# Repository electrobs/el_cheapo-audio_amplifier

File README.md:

# EL CHEAPO AMP

---
    AUTHOR: R.R. Moore (original design), John Convertino(revised)   
    
    DATE: 2020.12.23   
    
    DETAILS: Cheap 2N3055 amplifier using old power supplies for the base. Dual channel opamp version.
---

### DIRECTORY
#### models
3D models
* back_panel.stl  - Back panel for amplifier
* front_panel.stl - Front panel for amplifier
* FOOT.stl        - Foot for amplifier
* pcb.FCStd       - FreeCAD model of circuit board.
* pcb.step        - FreeCAD model of circuit board in STEP format.

#### schematic
KiCad Schematic and PCBS
* el_cheapo.pro - Main KiCAD project file

#### docs
Articles and datasheets used for the project.
* Audio-1964-11.pdf - Original el cheapo Article

### PARTS LIST
* N/A

### BUILD HELP
* This was designed to be built into a Acopian power supply. It depends on your power supply model as to how it will fit together... good luck!

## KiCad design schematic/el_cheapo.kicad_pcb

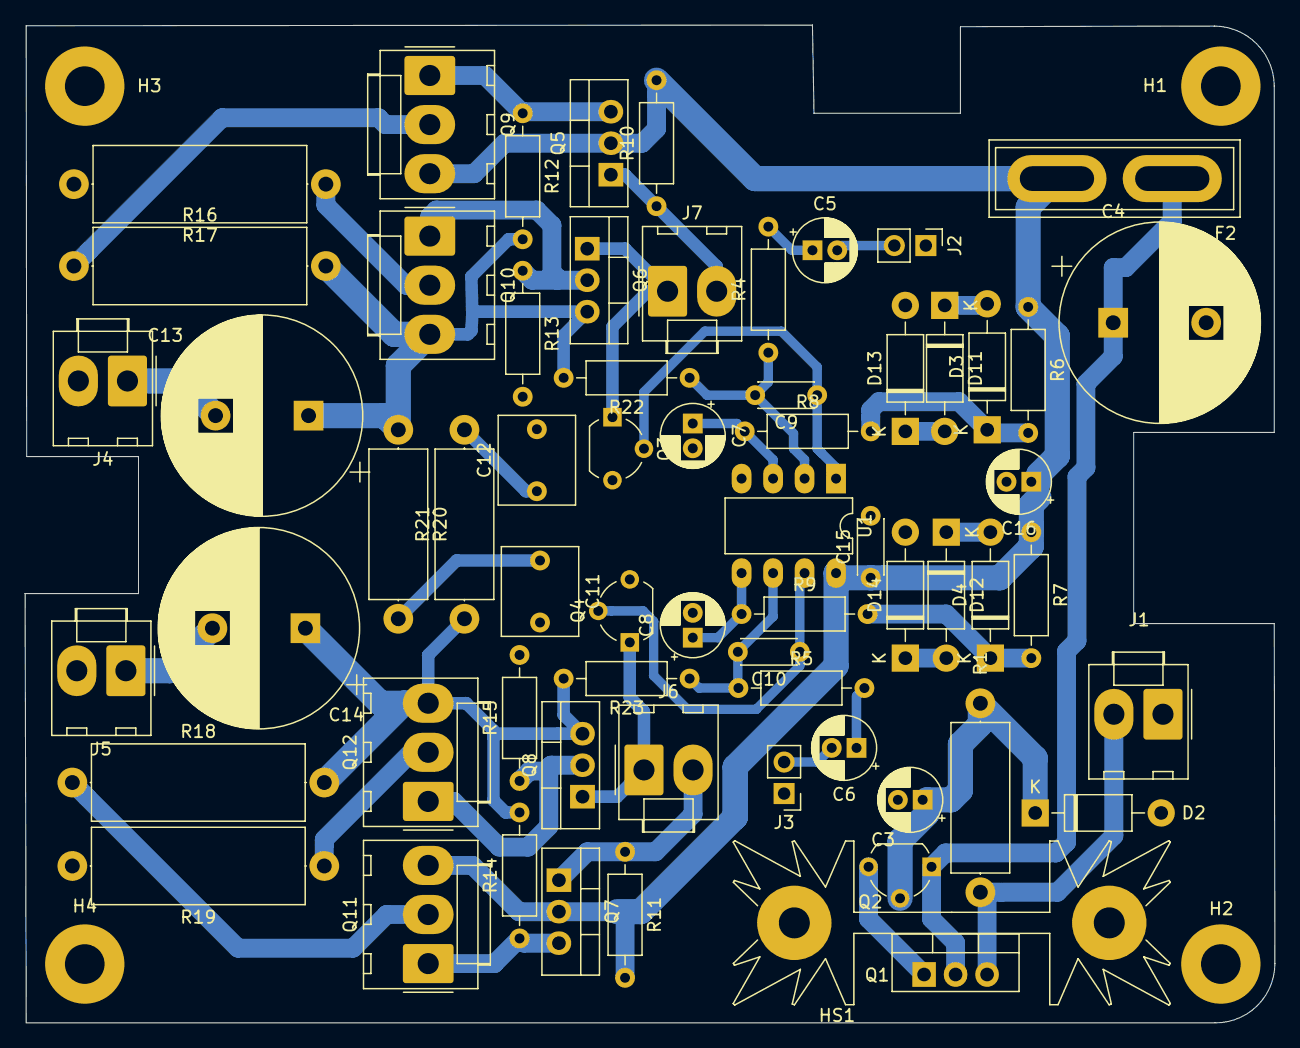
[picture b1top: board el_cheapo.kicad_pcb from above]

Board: 2 copper layers, 100.8 x 80.5 mm, 68 parts (0 on the bottom side), 40 nets.

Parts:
C3, C5, C6, C7, C8, C16: 10uF; CP_Radial_D5.0mm_P2.00mm
C4: 1000uF; CP_Radial_D16.0mm_P7.50mm
C9, C10: 1pF; C_Disc_D4.3mm_W1.9mm_P5.00mm
C11, C12: 100nF; C_Rect_L7.0mm_W6.0mm_P5.00mm
C13, C14: 2200uF; CP_Radial_D16.0mm_P7.50mm
C15: 0.1uF; C_Disc_D4.3mm_W1.9mm_P5.00mm
D2: 39V; D_DO-41_SOD81_P10.16mm_Horizontal
D3, D4: 1N47xxA; D_DO-41_SOD81_P10.16mm_Horizontal
D11, D12, D13, D14: 1N4001; D_DO-41_SOD81_P10.16mm_Horizontal
F2: 2A; Fuse_Blade_ATO_directSolder
H1, H2, H3, H4: MountingHole_Pad; MountingHole_3.2mm_M3_Pad
HS1: Heatsink; Heatsink_Fischer_SK104-STC-STIC_35x13mm_2xDrill2.5mm
J1, J4, J5, J6, J7: Conn_01x02; Molex_KK-396_A-41791-0002_1x02_P3.96mm_Vertical
J2, J3: Conn_01x02; PinHeader_1x02_P2.54mm_Vertical
Q1, Q6, Q8: TIP32A; TO-220-3_Vertical
Q2: 2N3904; TO-92_Wide
Q3, Q4: 2N3906; TO-92_Wide
Q5, Q7: TIP31A; TO-220-3_Vertical
Q9, Q10, Q11, Q12: 2N3055; Molex_KK-396_A-41791-0003_1x03_P3.96mm_Vertical
R1: 820R 2W; R_Axial_DIN0414_L11.9mm_D4.5mm_P15.24mm_Horizontal
R4, R5: 47k; R_Axial_DIN0207_L6.3mm_D2.5mm_P10.16mm_Horizontal
R6, R7: 22K; R_Axial_DIN0207_L6.3mm_D2.5mm_P10.16mm_Horizontal
R8, R9: 100K; R_Axial_DIN0207_L6.3mm_D2.5mm_P10.16mm_Horizontal
R10: 1k; R_Axial_DIN0207_L6.3mm_D2.5mm_P10.16mm_Horizontal
R11: 1K; R_Axial_DIN0207_L6.3mm_D2.5mm_P10.16mm_Horizontal
R12, R13, R14, R15: 270; R_Axial_DIN0207_L6.3mm_D2.5mm_P10.16mm_Horizontal
R16, R17, R18, R19: 0R47 1W; R_Axial_DIN0617_L17.0mm_D6.0mm_P20.32mm_Horizontal
R20, R21: 18R 1W; R_Axial_DIN0414_L11.9mm_D4.5mm_P15.24mm_Horizontal
R22, R23: 470k; R_Axial_DIN0207_L6.3mm_D2.5mm_P10.16mm_Horizontal
U1: NE5532; DIP-8_W7.62mm_LongPads

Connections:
/amp/+V: C15.1, C16.1, F2.1, Q5.2, Q7.2, Q9.3, Q11.3, R6.1, R7.1, R10.2, R11.2, U1.8
GND: C3.2, C4.2, C7.2, C8.2, C11.2, C12.2, C15.2, C16.2, D2.2, D13.2, D14.2, H1.1, H2.1, H3.1, H4.1, J1.1, J2.1, J3.1, J4.2, J5.2, Q3.3, Q4.3, R13.2, R15.2, R17.2, R19.2, U1.4
unnamed: J1.2, Q1.3, R1.1
unnamed: C3.1, D2.1, Q2.2, R1.2
unnamed: C4.1, F2.2, Q1.2, Q2.1
unnamed: C5.1, R4.2
unnamed: C5.2, J2.2
unnamed: C6.1, R5.2
unnamed: C6.2, J3.2
unnamed: C7.1, R8.1, U1.3
unnamed: C8.1, R9.1, U1.5
unnamed: C9.1, Q3.2, U1.1
unnamed: C9.2, R4.1, R22.1, U1.2
unnamed: C10.1, Q4.2, U1.7
unnamed: C10.2, R5.1, R23.1, U1.6
unnamed: C11.1, R20.2
unnamed: C12.1, R21.2
unnamed: C13.1, Q6.3, Q10.3, R12.2, R16.2, R20.1, R22.2
unnamed: C13.2, J4.1
unnamed: C14.1, Q8.3, Q12.3, R14.2, R18.2, R21.1, R23.2
unnamed: C14.2, J5.1
unnamed: D3.1, R6.2, R8.2
unnamed: D4.1, R7.2, R9.2
unnamed: J7.2, Q5.1, R10.1
unnamed: J7.1, Q3.1, Q6.1
unnamed: J6.2, Q7.1, R11.1
unnamed: J6.1, Q4.1, Q8.1
unnamed: D3.2, D11.1
unnamed: D11.2, D13.1
unnamed: D4.2, D12.1
unnamed: D12.2, D14.1
unnamed: Q1.1, Q2.3
unnamed: Q5.3, Q9.1, R12.1
unnamed: Q9.2, R16.1
unnamed: Q6.2, Q10.1, R13.1
unnamed: Q10.2, R17.1
unnamed: Q7.3, Q11.1, R14.1
unnamed: Q11.2, R18.1
unnamed: Q8.2, Q12.1, R15.1
unnamed: Q12.2, R19.1

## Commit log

2021-02-26 added WIP warning
2021-02-26 removed kicad file
2021-03-07 updated a few values based on the final parts used
2021-03-07 added pdf of schematic
2021-05-20 added details to readme
2021-05-20 fixed table... for now
2021-07-14 altered boards to fit dynaco amps of a similar design.
2021-08-01 first decent version of dual channel opamp version.
2021-08-03 updated dynaco footprint. First try wasn't perfect. This offers some flexability by using oblong holes.
2021-08-03 updated readme, and removed sim since its different from this design.
2021-08-03 removed pdf schematic from original design. Added zener opamp info doc.
2021-08-08 cleanup and remove resistor
2024-03-25 fixed for github
